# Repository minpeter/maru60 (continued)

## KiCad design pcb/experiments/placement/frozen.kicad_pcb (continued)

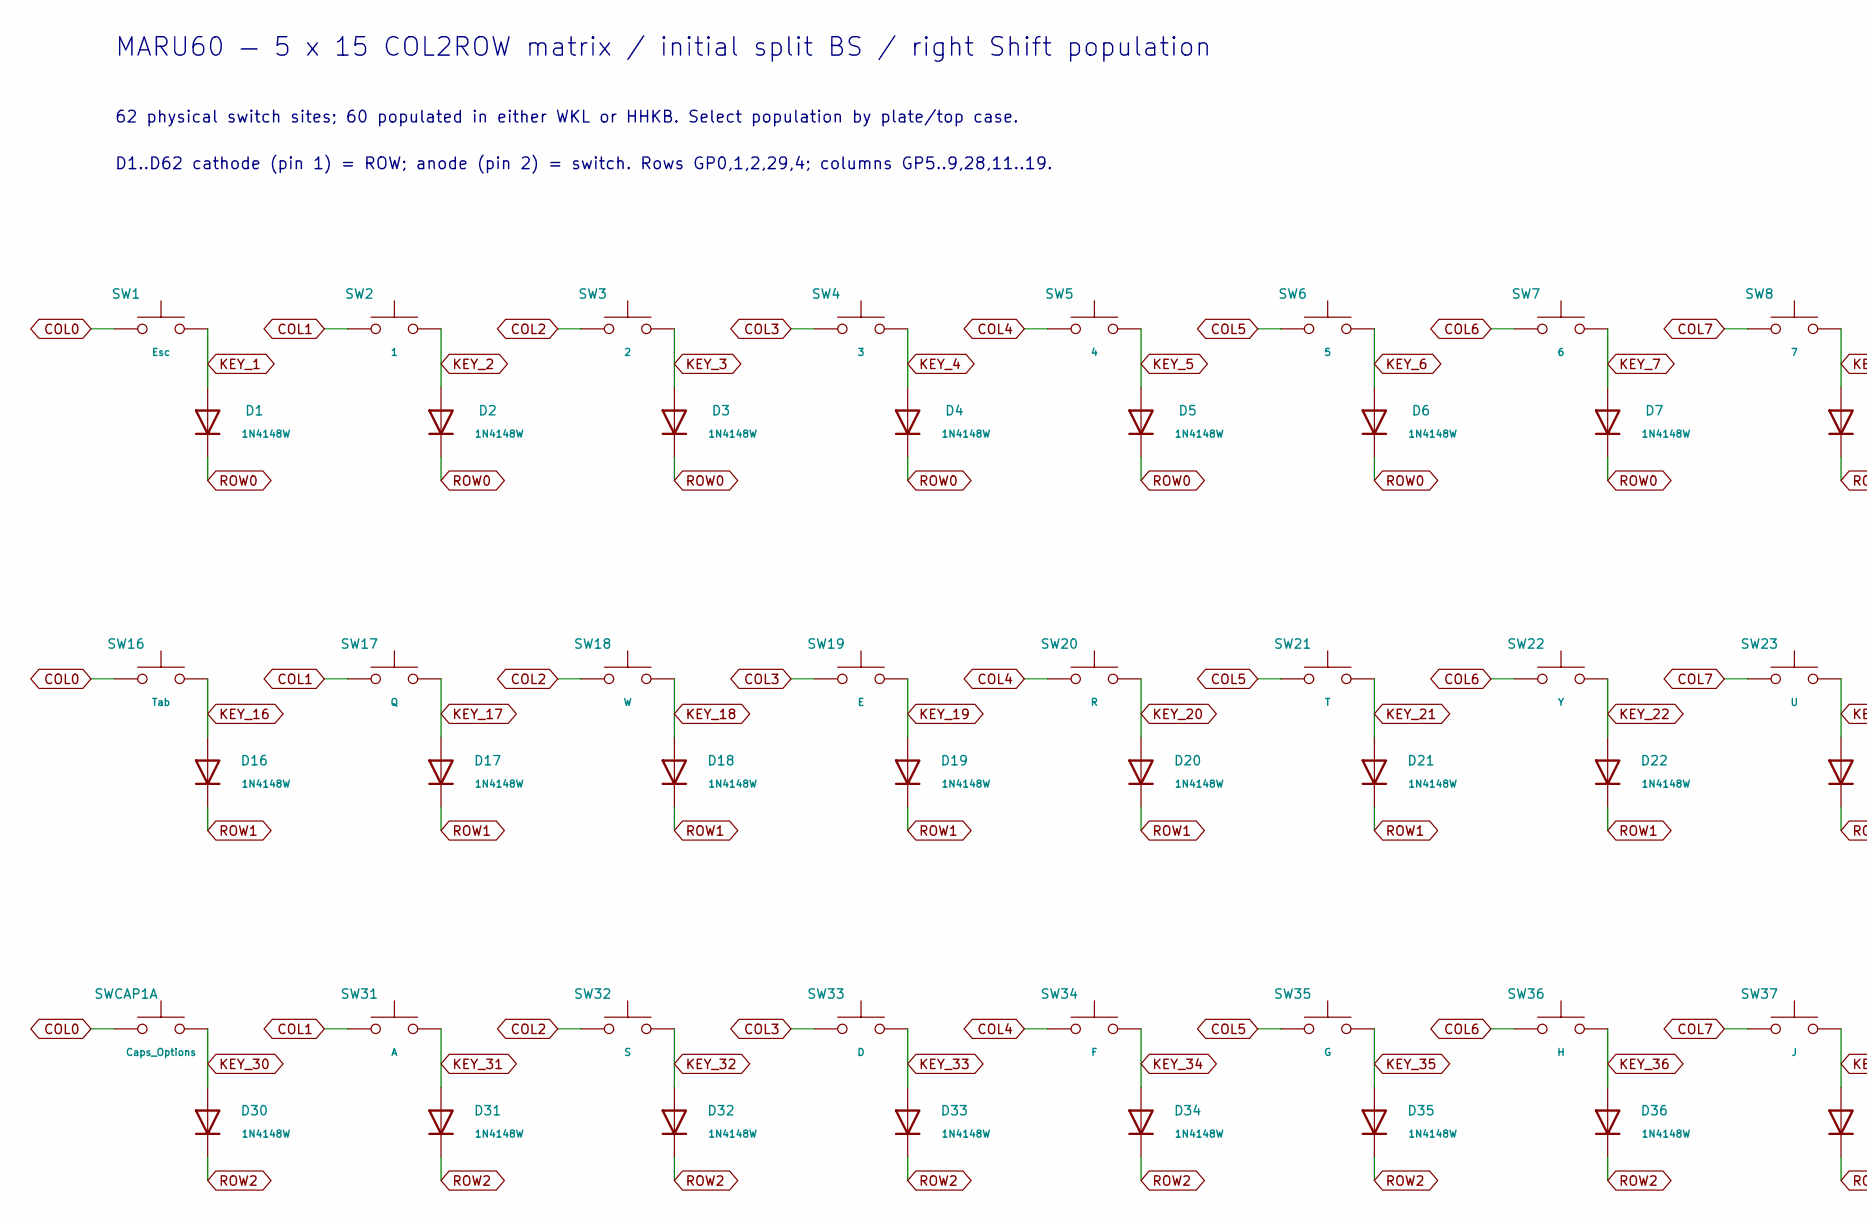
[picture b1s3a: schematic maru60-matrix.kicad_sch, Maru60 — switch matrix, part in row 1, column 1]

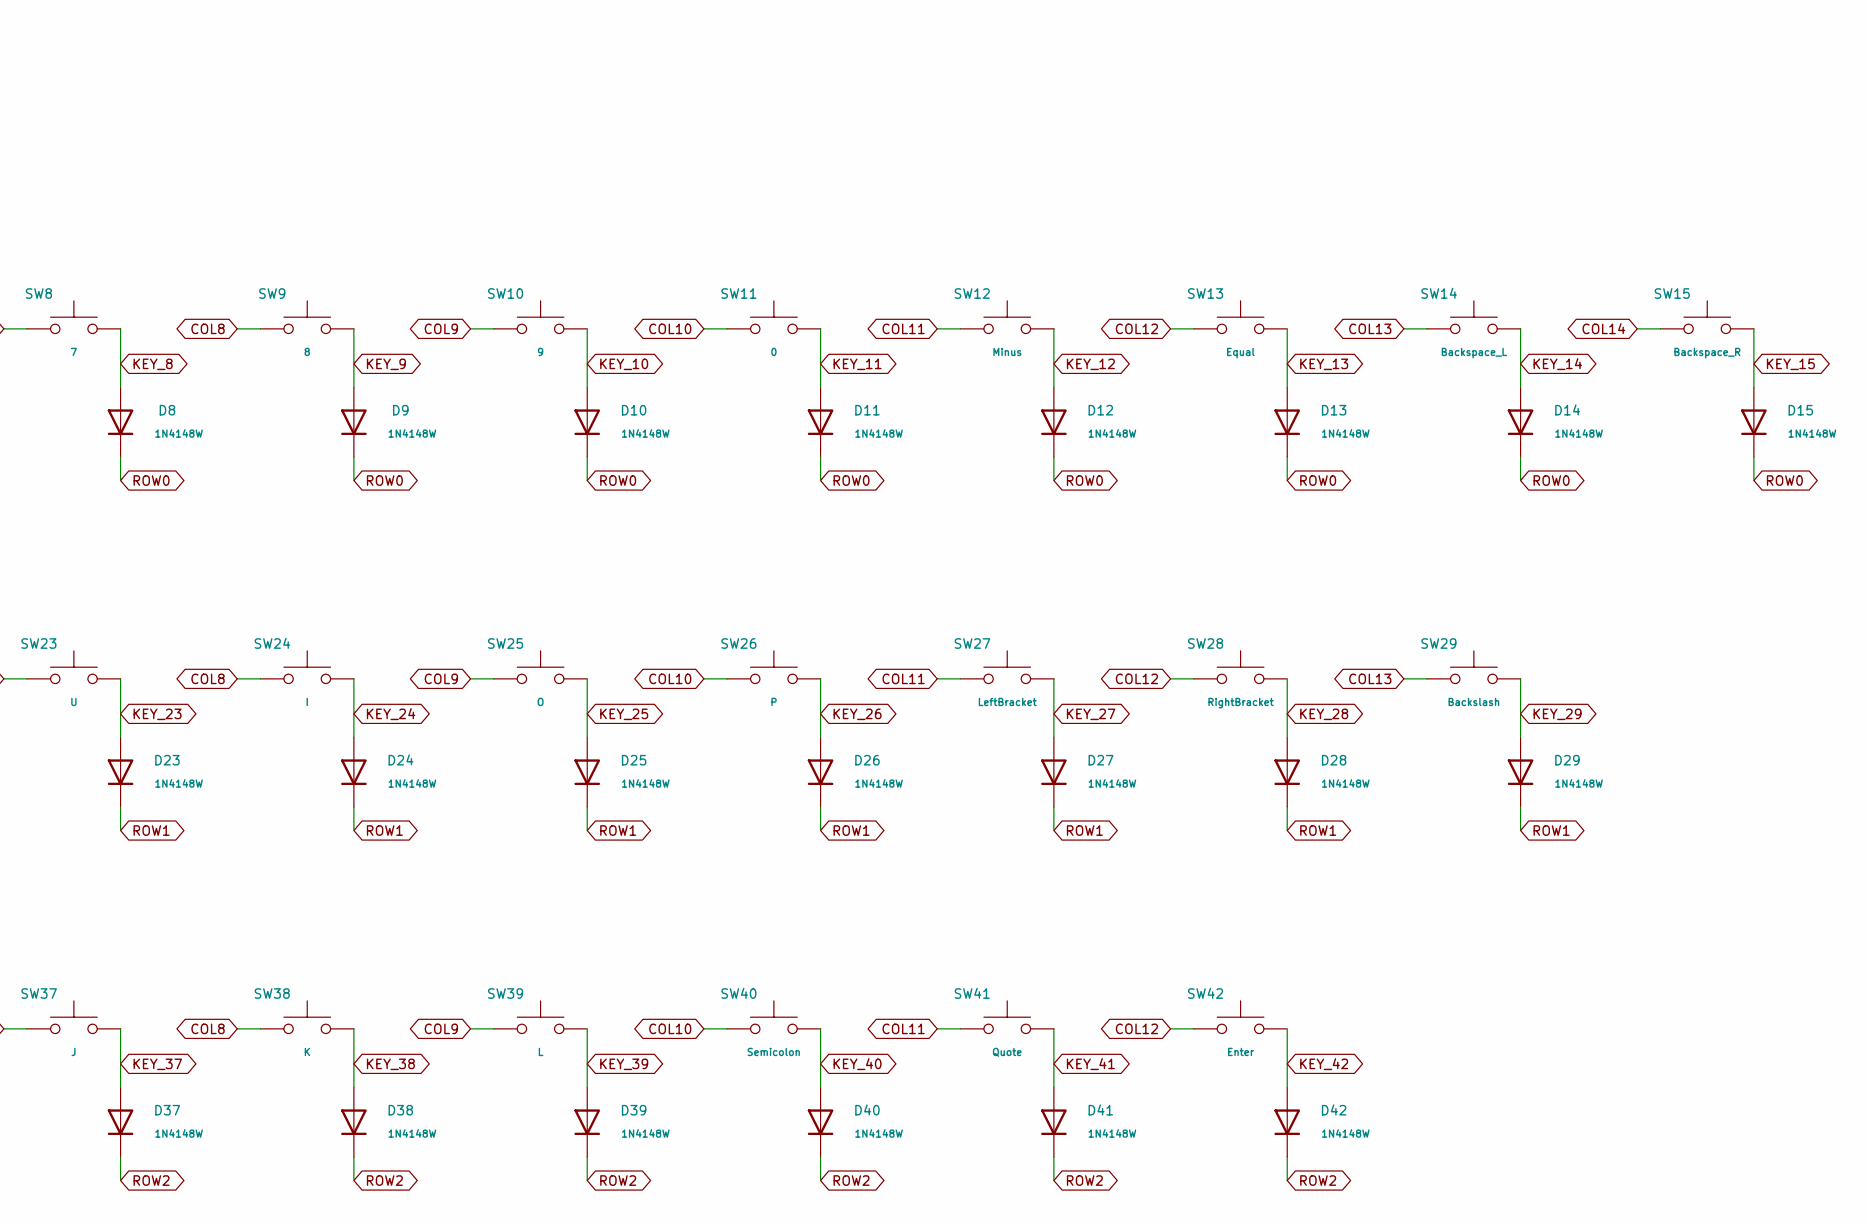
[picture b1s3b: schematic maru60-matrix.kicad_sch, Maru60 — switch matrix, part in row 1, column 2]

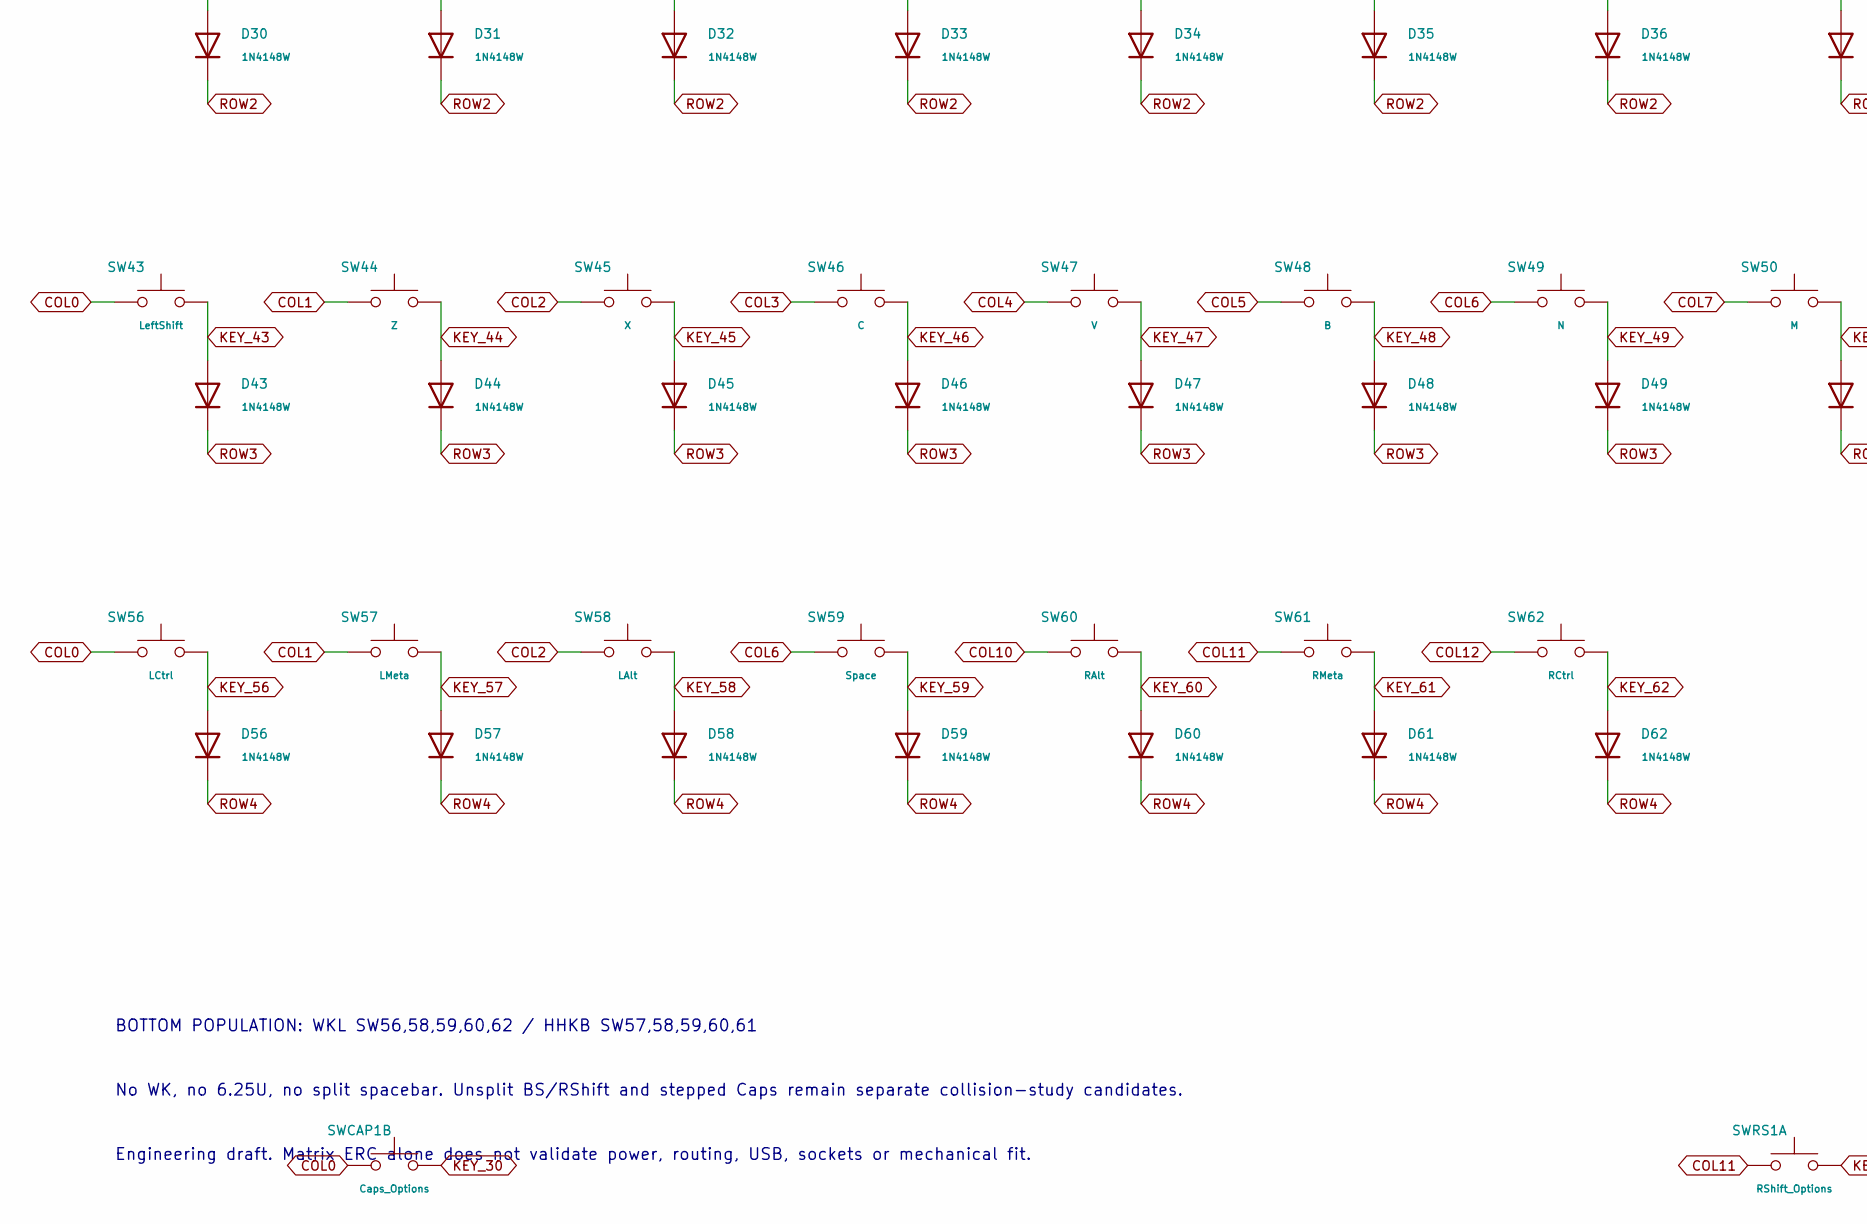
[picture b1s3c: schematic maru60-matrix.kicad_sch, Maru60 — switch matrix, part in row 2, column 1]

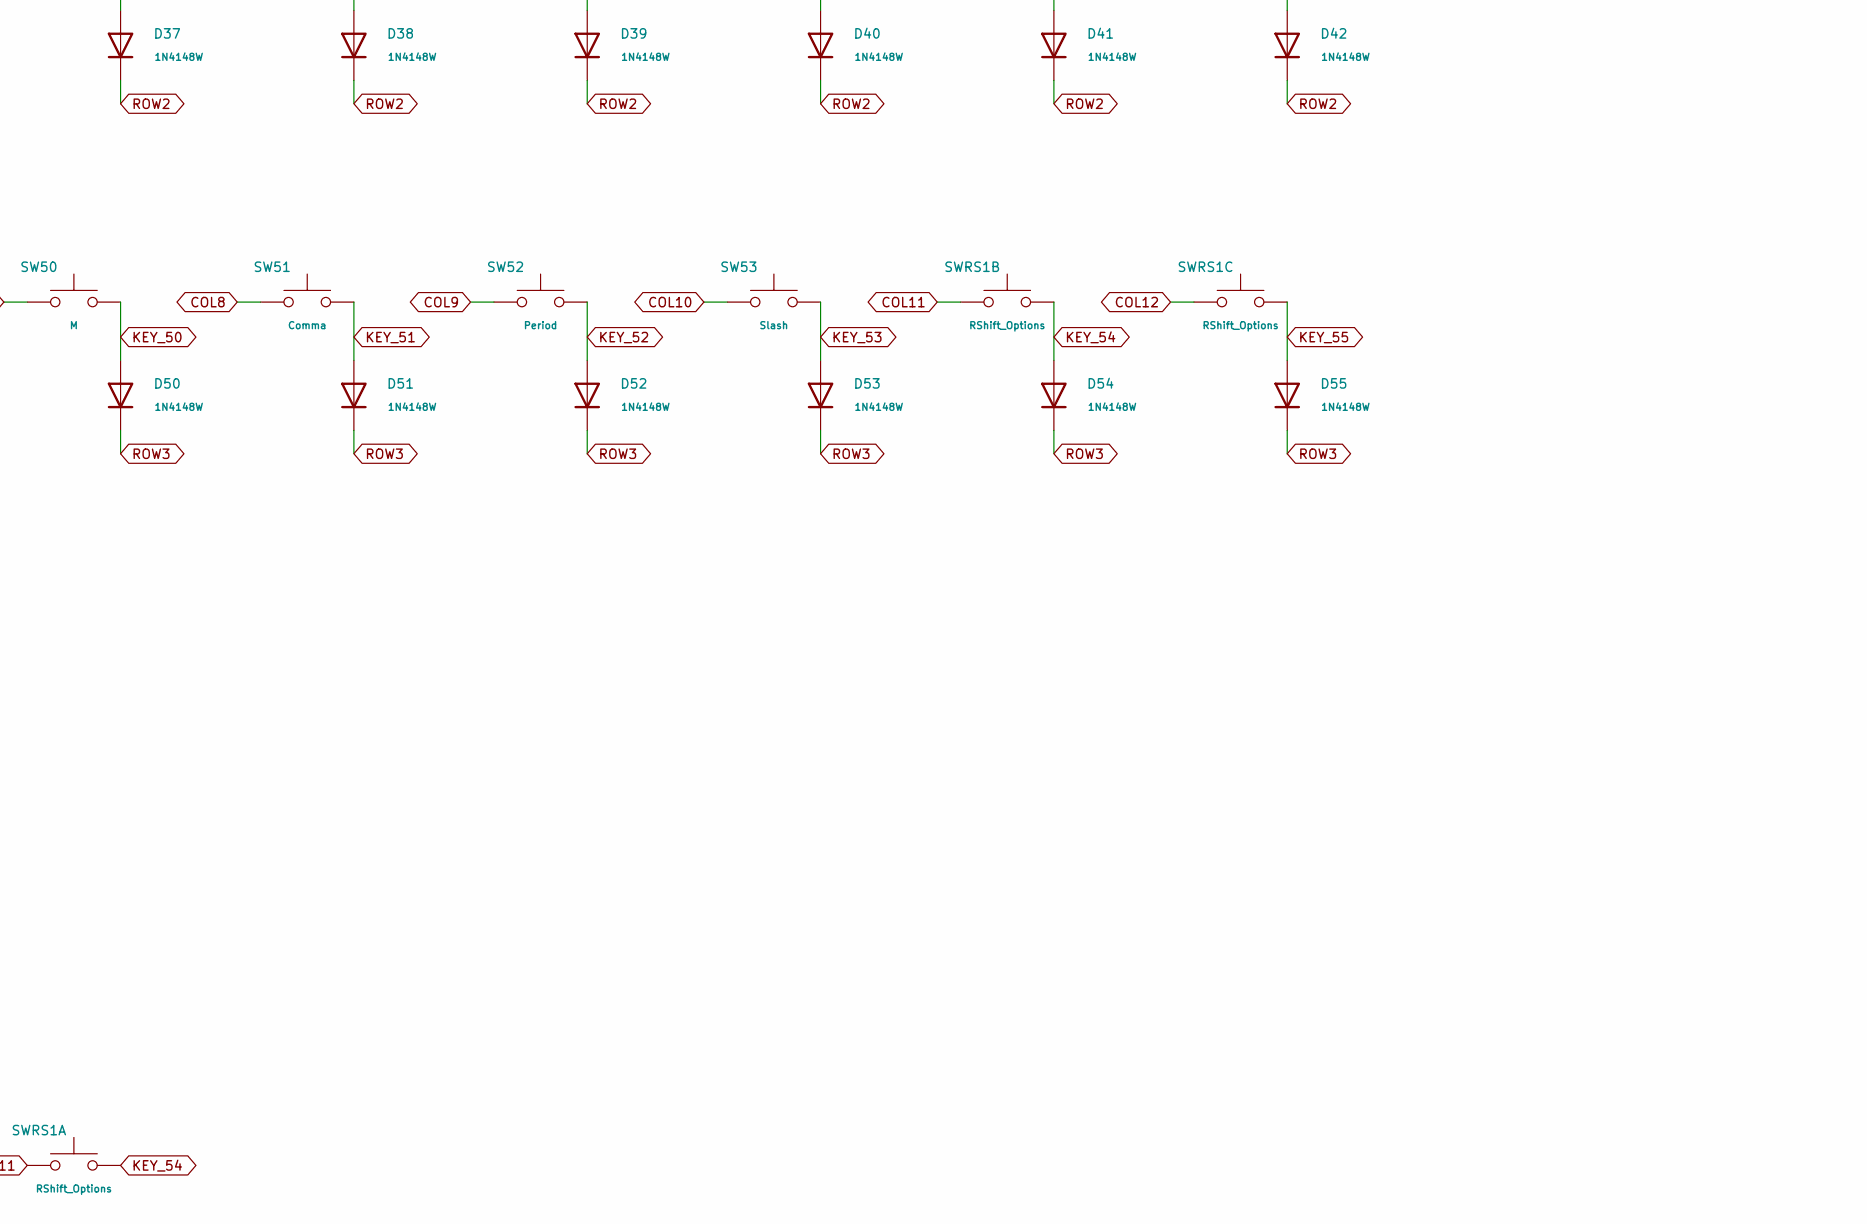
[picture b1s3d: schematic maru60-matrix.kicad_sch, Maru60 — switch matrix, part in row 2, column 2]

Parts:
D1, D2, D3, D4, D5, D6, D7, D8, D9, D10, D11, D12, D13, D14, D15, D16, D17, D18, D19, D20, D21, D22, D23, D24, D25, D26, D27, D28, D29, D30, D31, D32, D33, D34, D35, D36, D37, D38, D39, D40, D41, D42, D43, D44, D45, D46, D47, D48, D49, D50, D51, D52, D53, D54, D55, D56, D57, D58, D59, D60, D61, D62: 1N4148W; D_SOD-123
SW1: Esc; MX-Hotswap-1U
SW2: 1; MX-Hotswap-1U
SW3: 2; MX-Hotswap-1U
SW4: 3; MX-Hotswap-1U
SW5: 4; MX-Hotswap-1U
SW6: 5; MX-Hotswap-1U
SW7: 6; MX-Hotswap-1U
SW8: 7; MX-Hotswap-1U
SW9: 8; MX-Hotswap-1U
SW10: 9; MX-Hotswap-1U
SW11: 0; MX-Hotswap-1U
SW12: Minus; MX-Hotswap-1U
SW13: Equal; MX-Hotswap-1U
SW14: Backspace_L; MX-Hotswap-1U
SW15: Backspace_R; MX-Hotswap-1U
SW16: Tab; MX-Hotswap-1U
SW17: Q; MX-Hotswap-1U
SW18: W; MX-Hotswap-1U
SW19: E; MX-Hotswap-1U
SW20: R; MX-Hotswap-1U
SW21: T; MX-Hotswap-1U
SW22: Y; MX-Hotswap-1U
SW23: U; MX-Hotswap-1U
SW24: I; MX-Hotswap-1U
SW25: O; MX-Hotswap-1U
SW26: P; MX-Hotswap-1U
SW27: LeftBracket; MX-Hotswap-1U
SW28: RightBracket; MX-Hotswap-1U
SW29: Backslash; MX-Hotswap-1U
SW31: A; MX-Hotswap-1U
SW32: S; MX-Hotswap-1U
SW33: D; MX-Hotswap-1U
SW34: F; MX-Hotswap-1U
SW35: G; MX-Hotswap-1U
SW36: H; MX-Hotswap-1U
SW37: J; MX-Hotswap-1U
SW38: K; MX-Hotswap-1U
SW39: L; MX-Hotswap-1U
SW40: Semicolon; MX-Hotswap-1U
SW41: Quote; MX-Hotswap-1U
SW42: Enter; MX-Hotswap-2.25U-4L-NPTH
SW43: LeftShift; MX-Hotswap-2.25U-4L-NPTH
SW44: Z; MX-Hotswap-1U
SW45: X; MX-Hotswap-1U
SW46: C; MX-Hotswap-1U
SW47: V; MX-Hotswap-1U
SW48: B; MX-Hotswap-1U
SW49: N; MX-Hotswap-1U
SW50: M; MX-Hotswap-1U
SW51: Comma; MX-Hotswap-1U
SW52: Period; MX-Hotswap-1U
SW53: Slash; MX-Hotswap-1U
SW56: LCtrl; MX-Hotswap-1U
SW57: LMeta; MX-Hotswap-1U
SW58: LAlt; MX-Hotswap-1U
SW59: Space; MX-Hotswap-7U-4L-NPTH-StabRot180
SW60: RAlt; MX-Hotswap-1U
SW61: RMeta; MX-Hotswap-1U
SW62: RCtrl; MX-Hotswap-1U
SWCAP1: Caps_Options; MX_Study_Caps_Normal_or_Stepped
SWRS1: RShift_Options; MX_Study_RShift_2.75U_or_1.75U_1U

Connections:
COL0: SW1.1, SW16.1, SW43.1, SW56.1, SWCAP1.1, SWCAP1.3 (1); also elsewhere on the board
COL1: SW2.1, SW17.1, SW31.1, SW44.1, SW57.1; also elsewhere on the board
COL2: SW3.1, SW18.1, SW32.1, SW45.1, SW58.1; also elsewhere on the board
COL7: SW8.1, SW23.1, SW37.1, SW50.1; also elsewhere on the board
COL8: SW9.1, SW24.1, SW38.1, SW51.1; also elsewhere on the board
COL9: SW10.1, SW25.1, SW39.1, SW52.1; also elsewhere on the board
COL13: SW14.1, SW29.1; also elsewhere on the board
COL14: SW15.1; also elsewhere on the board
KEY_1: D1.2 (A), SW1.2
KEY_2: D2.2 (A), SW2.2
KEY_3: D3.2 (A), SW3.2
KEY_4: D4.2 (A), SW4.2
KEY_5: D5.2 (A), SW5.2
KEY_6: D6.2 (A), SW6.2
KEY_7: D7.2 (A), SW7.2
KEY_8: D8.2 (A), SW8.2
KEY_9: D9.2 (A), SW9.2
KEY_10: D10.2 (A), SW10.2
KEY_11: D11.2 (A), SW11.2
KEY_12: D12.2 (A), SW12.2
KEY_13: D13.2 (A), SW13.2
KEY_14: D14.2 (A), SW14.2
KEY_15: D15.2 (A), SW15.2
KEY_16: D16.2 (A), SW16.2
KEY_17: D17.2 (A), SW17.2
KEY_18: D18.2 (A), SW18.2
KEY_19: D19.2 (A), SW19.2
KEY_20: D20.2 (A), SW20.2
KEY_21: D21.2 (A), SW21.2
KEY_22: D22.2 (A), SW22.2
KEY_23: D23.2 (A), SW23.2
KEY_24: D24.2 (A), SW24.2
KEY_25: D25.2 (A), SW25.2
KEY_26: D26.2 (A), SW26.2
KEY_27: D27.2 (A), SW27.2
KEY_28: D28.2 (A), SW28.2
KEY_29: D29.2 (A), SW29.2
KEY_30: D30.2 (A), SWCAP1.2, SWCAP1.4 (2)
KEY_31: D31.2 (A), SW31.2
KEY_32: D32.2 (A), SW32.2
KEY_33: D33.2 (A), SW33.2
KEY_34: D34.2 (A), SW34.2
KEY_35: D35.2 (A), SW35.2
KEY_36: D36.2 (A), SW36.2
KEY_37: D37.2 (A), SW37.2
KEY_38: D38.2 (A), SW38.2
KEY_39: D39.2 (A), SW39.2
KEY_40: D40.2 (A), SW40.2
KEY_41: D41.2 (A), SW41.2
KEY_42: D42.2 (A), SW42.2
KEY_43: D43.2 (A), SW43.2
KEY_44: D44.2 (A), SW44.2
KEY_45: D45.2 (A), SW45.2
KEY_46: D46.2 (A), SW46.2
KEY_47: D47.2 (A), SW47.2
KEY_48: D48.2 (A), SW48.2
KEY_49: D49.2 (A), SW49.2
KEY_50: D50.2 (A), SW50.2
KEY_51: D51.2 (A), SW51.2
KEY_52: D52.2 (A), SW52.2
KEY_53: D53.2 (A), SW53.2
KEY_54: D54.2 (A), SWRS1.2, SWRS1.4 (2)
KEY_55: D55.2 (A), SWRS1.6 (2)
KEY_56: D56.2 (A), SW56.2
KEY_57: D57.2 (A), SW57.2
KEY_58: D58.2 (A), SW58.2
KEY_59: D59.2 (A), SW59.2
KEY_60: D60.2 (A), SW60.2
KEY_61: D61.2 (A), SW61.2
KEY_62: D62.2 (A), SW62.2
ROW0: D1.1 (K), D2.1 (K), D3.1 (K), D4.1 (K), D5.1 (K), D6.1 (K), D7.1 (K), D8.1 (K), D9.1 (K), D10.1 (K), D11.1 (K), D12.1 (K), D13.1 (K), D14.1 (K), D15.1 (K); also elsewhere on the board
ROW1: D16.1 (K), D17.1 (K), D18.1 (K), D19.1 (K), D20.1 (K), D21.1 (K), D22.1 (K), D23.1 (K), D24.1 (K), D25.1 (K), D26.1 (K), D27.1 (K), D28.1 (K), D29.1 (K); also elsewhere on the board
ROW2: D30.1 (K), D31.1 (K), D32.1 (K), D33.1 (K), D34.1 (K), D35.1 (K), D36.1 (K), D37.1 (K), D38.1 (K), D39.1 (K), D40.1 (K), D41.1 (K), D42.1 (K); also elsewhere on the board
ROW3: D43.1 (K), D44.1 (K), D45.1 (K), D46.1 (K), D47.1 (K), D48.1 (K), D49.1 (K), D50.1 (K), D51.1 (K), D52.1 (K), D53.1 (K), D54.1 (K), D55.1 (K); also elsewhere on the board
ROW4: D56.1 (K), D57.1 (K), D58.1 (K), D59.1 (K), D60.1 (K), D61.1 (K), D62.1 (K); also elsewhere on the board

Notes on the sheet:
MARU60 — 5 x 15 COL2ROW matrix / initial split BS / right Shift population
62 physical switch sites; 60 populated in either WKL or HHKB. Select population by plate/top case.
D1..D62 cathode (pin 1) = ROW; anode (pin 2) = switch. Rows GP0,1,2,29,4; columns GP5..9,28,11..19.
BOTTOM POPULATION: WKL SW56,58,59,60,62 / HHKB SW57,58,59,60,61
No WK, no 6.25U, no split spacebar. Unsplit BS/RShift and stepped Caps remain separate collision-study candidates.
Engineering draft. Matrix ERC alone does not validate power, routing, USB, sockets or mechanical fit.

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
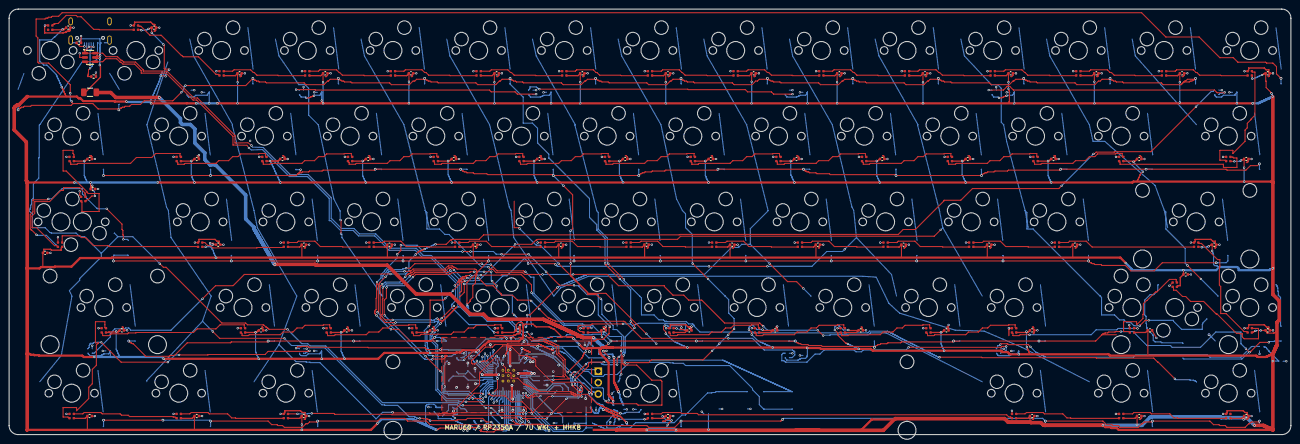
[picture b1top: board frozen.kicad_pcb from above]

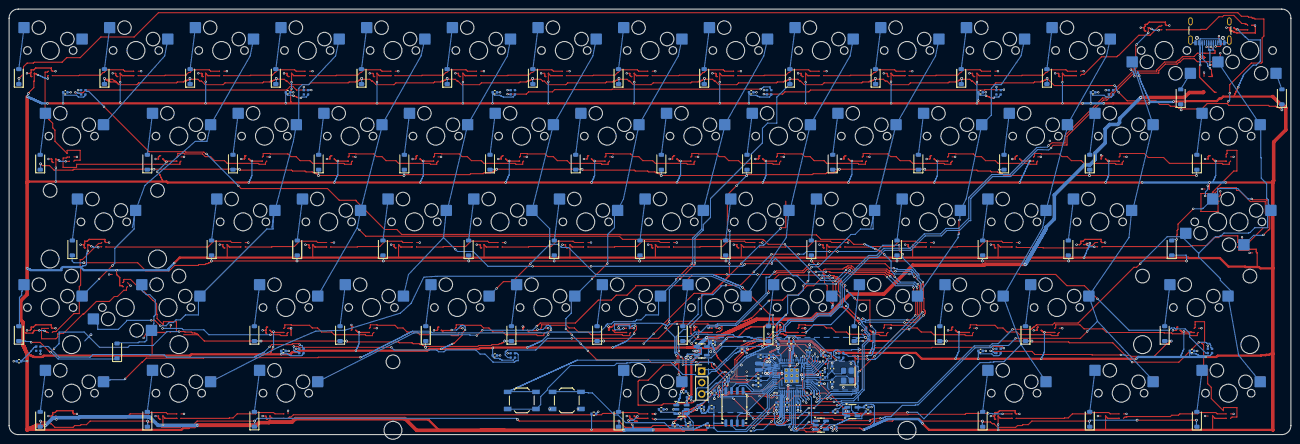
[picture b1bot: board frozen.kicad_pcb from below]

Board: 4 copper layers, 285.0 x 94.6 mm, 328 parts (195 on the bottom side), 193 nets.

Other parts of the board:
STAB_RS1: (no value)

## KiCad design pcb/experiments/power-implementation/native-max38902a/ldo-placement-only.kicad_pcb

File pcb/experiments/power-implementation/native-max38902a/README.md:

Isolated BOM/land-pattern study, NOT FOR FAB. See ../IMPLEMENTATION.md and ../RESET-RECOVERY.md. Electrical pin/net endpoints identical to independently reviewed correction; exact MPN/footprint metadata and C14268nF-to10nF value differ. The placement-only PCB is NOT the main board and not routed.

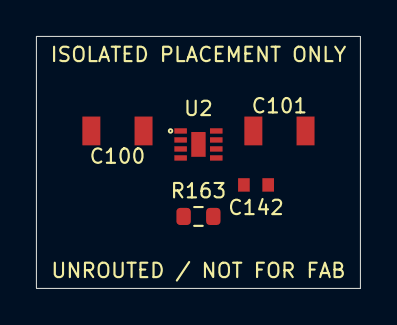
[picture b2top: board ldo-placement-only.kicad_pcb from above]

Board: 2 copper layers, 18.0 x 14.0 mm, 5 parts (0 on the bottom side), 4 nets, no tracks yet.

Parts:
C100, C101: GRM31CR71H475KA12L; Murata_GRM31_1206_Reflow_1.0x1.6_Gap1.9
C142: GRM1885C1H103JA01D; Murata_GRM18_0603_Reflow_0.65x0.75_Gap0.7
R163: TNPW060331K6BYEA; R_0603_1608Metric
U2: MAX38902AATA+T; MAX_T822-3C_90-0065_2x2_P0.5_EP0.8x1.38

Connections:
+3V3: C101.1, C142.1, R163.1, U2.6, U2.8
+4V_REG: C100.1, U2.1, U2.3
GND: C100.2, C101.2, R163.2, U2.2, U2.4, U2.9
LDO_BYP: C142.2, U2.7
